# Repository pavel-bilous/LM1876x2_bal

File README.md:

# Paralleled LM1876 amplifier with balanced input

LM1876 Overture Series amplifier with two paralleled integrated channels, balanced inputs, and THT/SMD components. Created using KiCad v5.

Benefits of using two channels in parallel include: 
- increase of the output drive capability of an amplifier (higher output current drive), 
- reduced voltage noise (better SNR), 
- and reduced output offset error.

Resources used to design this amp: 
official TI datasheet - [https://www.ti.com/lit/ds/symlink/lm1876.pdf](https://www.ti.com/lit/ds/symlink/lm1876.pdf)

## PCB rendered in 3d:

# Schematics notes:

This is balanced (or differential) implementation of the amplifier. Meaning, you will need to supply IN+ and IN- in addition to the GND for the input signal.
Each channel acts as a difference amplifier providing CMRR performance from the datasheet and limited by the precision of the feedback resistors - 0.1% resistors will give max theoretical CMRR of 66dB.
Inputs are DC coupled with 100u capacitors and form HP filter with R1||R2=1K giving fc=1.59Hz.
Power supply decoupling capacitors are sized according to the datasheet. Two small ceramic X7R type caps of 1uF or 2uF are located close to ICs pins. Two bigger caps are 1000uF aluminum electrolytic and located within close proximity of the IC. 

Because input resistance is 1K you will need to provide some sort of impedance matching to be able to interface from other devices. I have a few buffer designs on my GitHub.

The overall gain is configured to be 10V/V or 20dB. Such gain value allows designer a greater flexibility in choosing the previous stage.

Recommended power supply is dual 25V supply.

# PCB notes:

PCB was created by keeping following important points in mind:
- First elements that were placed next to the IC were decoupling ceramic capacitors. Those are SMD 1206 footpints with increased pad sizes that can be hand soldered. One of the capacitors was placed on the bottom side of the board to allow for shorter ground loop signal travel distance (distance from Vcc pin to capacitor, then to GND, then to the other capacitor, and finally to the Vee pin).
- Elements on the board were separated into two groups - one with low current to the right, and another with high current to the left of the IC). 
- Bottom layer is GND, top layer is power + signal. Certain deviations were needed to route power and MUTE/STBY signals. Top layer was poured with GND in between signal and power traces and stiched with vias to improve EMI performance.
- Two layer board with minimum track width of 0.3mm, clearance of 0.3mm, vias sized 0.3mm drill and 0.7mm ring for easy manufacturing.

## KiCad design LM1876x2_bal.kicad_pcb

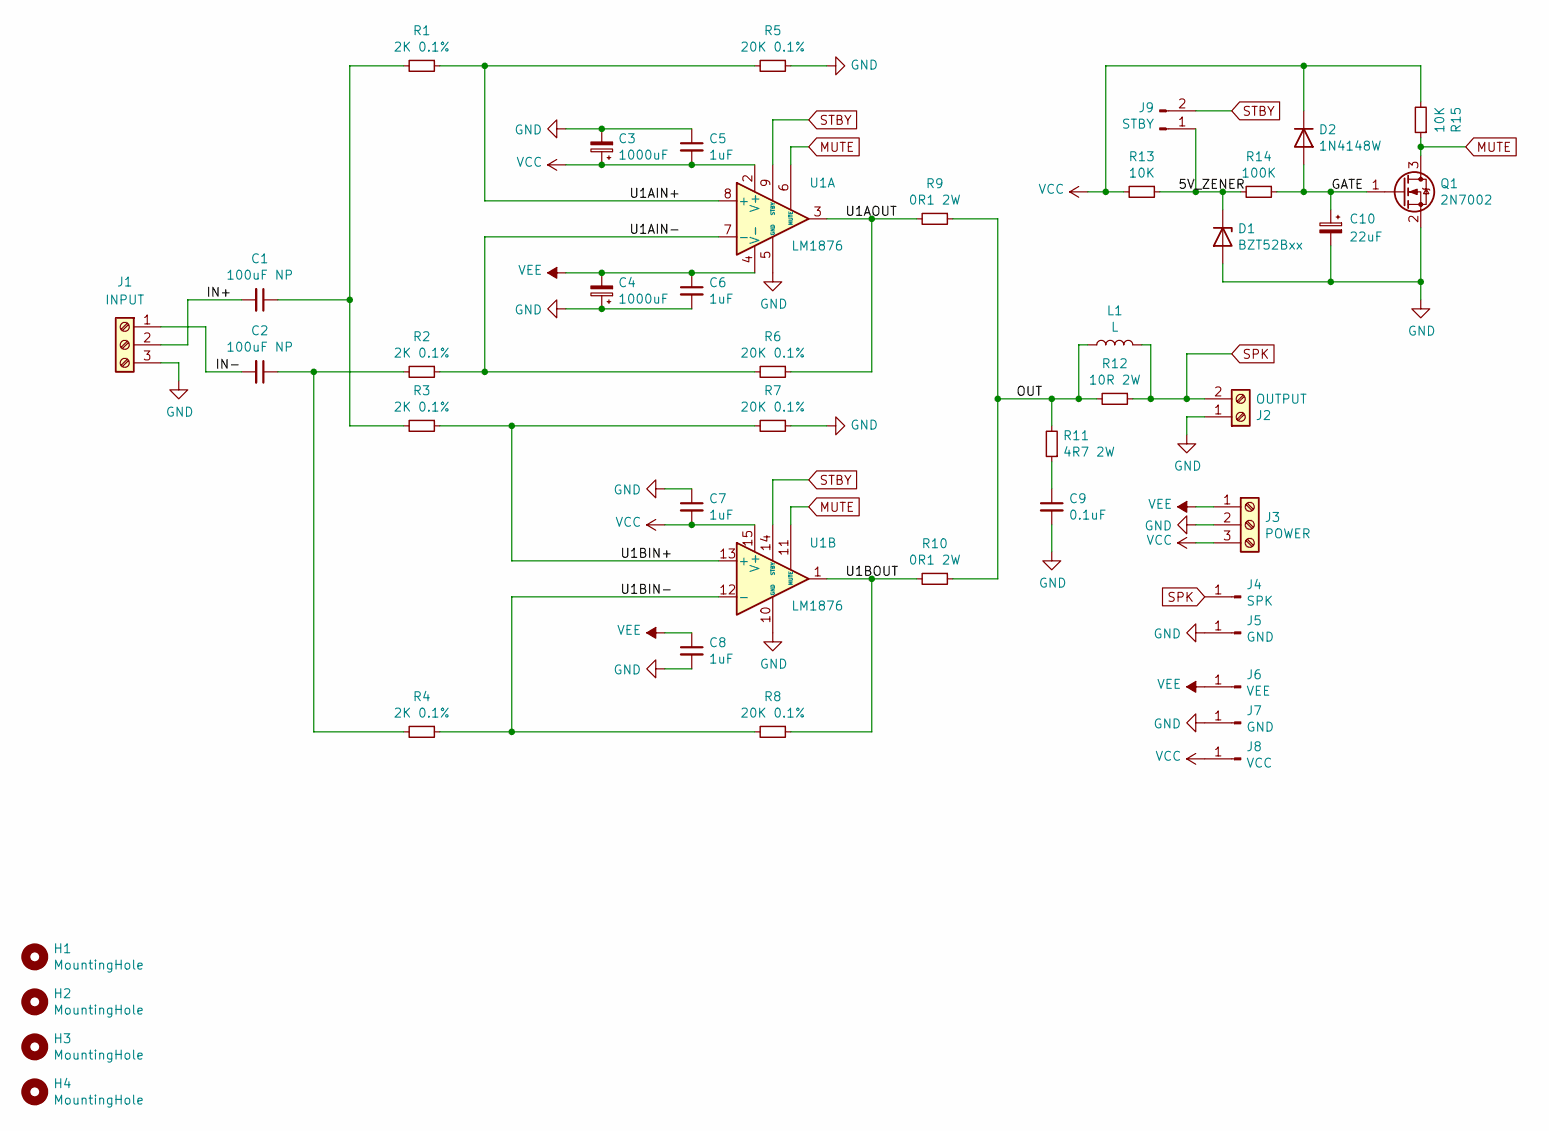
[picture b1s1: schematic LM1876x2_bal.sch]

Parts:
C1, C2: 100uF NP; C_Radial_D10.0mm_H16.0mm_P5.00mm
C3, C4: 1000uF; CP_Radial_D16.0mm_P7.50mm
C5, C6, C7, C8: 1uF; C_1206_3216Metric_Pad1.42x1.75mm_HandSolder
C9: 0.1uF; C_Rect_L7.2mm_W2.5mm_P5.00mm_FKS2_FKP2_MKS2_MKP2
C10: 22uF; CP_Radial_D6.3mm_P2.50mm
D1: BZT52Bxx; D_SOD-123
D2: 1N4148W; D_SOD-123
H1, H2, H3, H4: MountingHole; MountingHole_3.5mm_Pad_Via
J1: INPUT; TerminalBlock_ Amphenol_01_03_P3.50mm
J2: OUTPUT; TerminalBlock_CUI_01x02_P5.00mm
J3: POWER; TerminalBlock_CUI_01x03_P5.00mm
J4: SPK; Terminal_.25_PCB_TAB_TE_Connectivity_P5.08mm_
J5, J7: GND; Terminal_.25_PCB_TAB_TE_Connectivity_P5.08mm_
J6: VEE; Terminal_.25_PCB_TAB_TE_Connectivity_P5.08mm_
J8: VCC; Terminal_.25_PCB_TAB_TE_Connectivity_P5.08mm_
J9: STBY; PinHeader_1x02_P2.54mm_Vertical
L1: L; Inductor_DIY_flipped
Q1: 2N7002; SOT-23
R1, R2, R3, R4: 2K 0.1%; R_1206_3216Metric_Pad1.42x1.75mm_HandSolder
R5, R6, R7, R8: 20K 0.1%; R_1206_3216Metric_Pad1.42x1.75mm_HandSolder
R9, R10: 0R1 2W; R_Axial_DIN0414_L11.9mm_D4.5mm_P15.24mm_Horizontal
R11: 4R7 2W; R_Axial_DIN0414_L11.9mm_D4.5mm_P15.24mm_Horizontal
R12: 10R 2W; R_Axial_DIN0414_L11.9mm_D4.5mm_P15.24mm_Horizontal
R13, R15: 10K; R_1206_3216Metric_Pad1.42x1.75mm_HandSolder
R14: 100K; R_1206_3216Metric_Pad1.42x1.75mm_HandSolder
U1: LM1876; TO-220-15_P2.54x2.54mm_StaggerOdd_Lead4.58mm_Vertical

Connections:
/5V_ZENER: D1.1 (K), J9.1, R13.1, R14.2
/GATE: C10.1, D2.2 (A), Q1.1 (G), R14.1
/IN+: C1.2, J1.2
/IN-: C2.2, J1.1
/OUT: L1.1, R9.1, R10.1, R11.2, R12.2
/U1AIN+: R1.1, R5.2, U1.8 (+)
/U1AIN-: R2.1, R6.2, U1.7 (-)
/U1AOUT: R6.1, R9.2, U1.3
/U1BIN+: R3.1, R7.2, U1.13 (+)
/U1BIN-: R4.1, R8.2, U1.12 (-)
/U1BOUT: R8.1, R10.2, U1.1
GND: C3.2, C4.1, C5.1, C6.2, C7.1, C8.2, C9.2, C10.2, D1.2 (A), J1.3, J2.1, J3.2, J5.1, J7.1, Q1.2 (S), R5.1, R7.1, U1.5 (GND), U1.10 (GND)
MUTE: Q1.3 (D), R15.1, U1.6 (MUTE), U1.11 (MUTE)
unnamed: C1.1, R1.2, R3.2
unnamed: C2.1, R2.2, R4.2
unnamed: C9.1, R11.1
SPK: J2.2, J4.1, L1.2, R12.1
STBY: J9.2, U1.9 (STBY), U1.14 (STBY)
VCC: C3.1, C5.2, C7.2, D2.1 (K), J3.3, J8.1, R13.2, R15.2, U1.2 (V+), U1.15 (V+)
VEE: C4.2, C6.1, C8.1, J3.1, J6.1, U1.4 (V-)

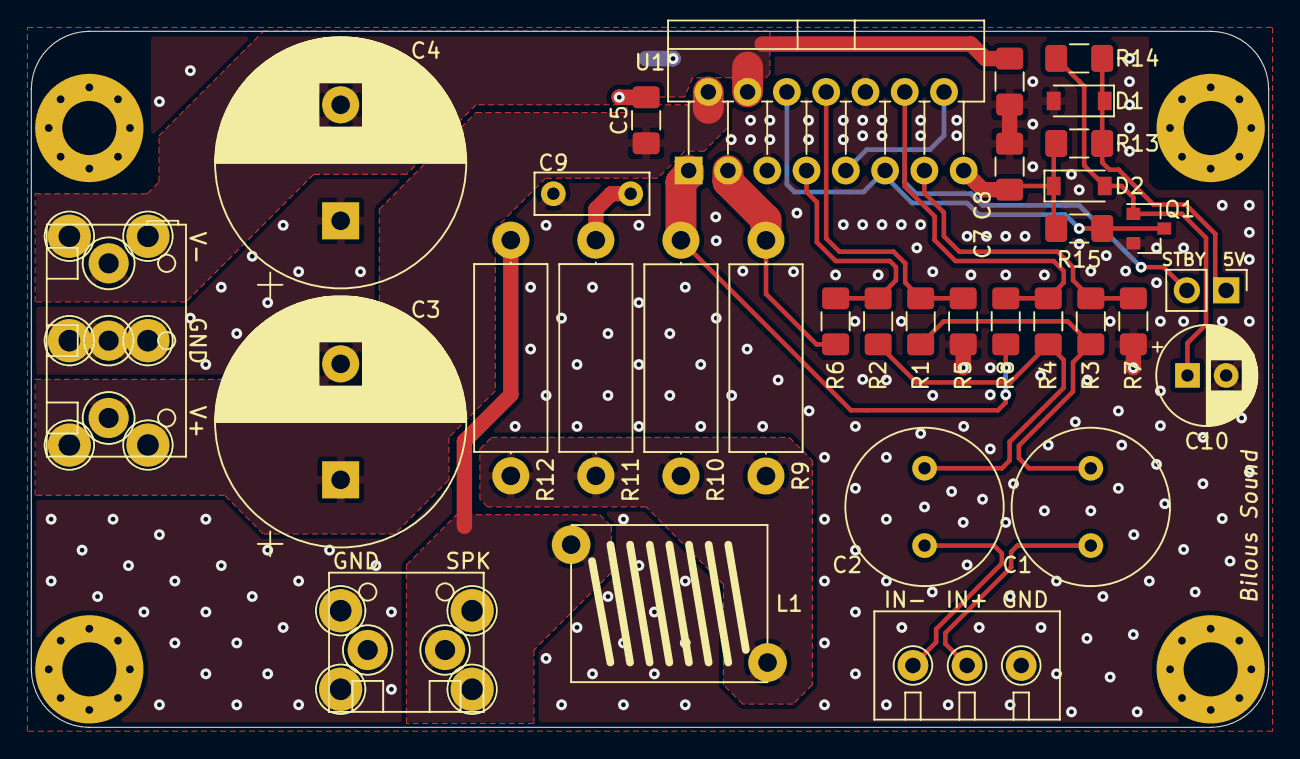
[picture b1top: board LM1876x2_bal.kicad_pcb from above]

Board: 2 copper layers, 80.0 x 45.0 mm, 43 parts (1 on the bottom side), 20 nets.

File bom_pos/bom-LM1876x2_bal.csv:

"Id";"Designator";"Package";"Quantity";"Designation";"Supplier and ref";
1;"Q1";"SOT-23";1;"2N7002";;;
2;"D2";"D_SOD-123";1;"1N4148W";;;
3;"R15,R13";"R_1206_3216Metric_Pad1.42x1.75mm_HandSolder";2;"10K";;;
4;"R14";"R_1206_3216Metric_Pad1.42x1.75mm_HandSolder";1;"100K";;;
5;"J9";"PinHeader_1x02_P2.54mm_Vertical";1;"STBY";;;
6;"D1";"D_SOD-123";1;"BZT52Bxx";;;
7;"C10";"CP_Radial_D6.3mm_P2.50mm";1;"22uF";;;
8;"R4,R3,R2,R1";"R_1206_3216Metric_Pad1.42x1.75mm_HandSolder";4;"2K 0.1%";;;
9;"J2";"TerminalBlock_CUI_01x02_P5.00mm";1;"OUTPUT";;;
10;"R9,R10";"R_Axial_DIN0414_L11.9mm_D4.5mm_P15.24mm_Horizontal";2;"0R1 2W";;;
11;"H4,H3,H2,H1";"MountingHole_3.5mm_Pad_Via";4;"MountingHole";;;
12;"U1";"TO-220-15_P2.54x2.54mm_StaggerOdd_Lead4.58mm_Vertical";1;"LM1876";;;
13;"R12";"R_Axial_DIN0414_L11.9mm_D4.5mm_P15.24mm_Horizontal";1;"10R 2W";;;
14;"R11";"R_Axial_DIN0414_L11.9mm_D4.5mm_P15.24mm_Horizontal";1;"4R7 2W";;;
15;"R8,R7,R6,R5";"R_1206_3216Metric_Pad1.42x1.75mm_HandSolder";4;"20K 0.1%";;;
16;"L1";"Inductor_DIY_flipped";1;"L";;;
17;"J8";"Terminal_.25_PCB_TAB_TE_Connectivity_P5.08mm_";1;"VCC";;;
18;"J7,J5";"Terminal_.25_PCB_TAB_TE_Connectivity_P5.08mm_";2;"GND";;;
19;"J6";"Terminal_.25_PCB_TAB_TE_Connectivity_P5.08mm_";1;"VEE";;;
20;"J4";"Terminal_.25_PCB_TAB_TE_Connectivity_P5.08mm_";1;"SPK";;;
21;"J3";"TerminalBlock_CUI_01x03_P5.00mm";1;"POWER";;;
22;"J1";"TerminalBlock_ Amphenol_01_03_P3.50mm";1;"INPUT";;;
23;"C9";"C_Rect_L7.2mm_W2.5mm_P5.00mm_FKS2_FKP2_MKS2_MKP2";1;"0.1uF";;;
24;"C8,C7,C6,C5";"C_1206_3216Metric_Pad1.42x1.75mm_HandSolder";4;"1uF";;;
25;"C4,C3";"CP_Radial_D16.0mm_P7.50mm";2;"1000uF";;;
26;"C2,C1";"C_Radial_D10.0mm_H16.0mm_P5.00mm";2;"100uF NP";;;

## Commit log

2023-05-08 gitignore file upload
2023-05-08 added licence terms
2023-05-09 revised readme
2023-05-09 added imgs
2023-05-09 rev2.0 updates include adding mute delay circuit to the board
2023-05-10 minor changes
2023-05-10 minor fixes
